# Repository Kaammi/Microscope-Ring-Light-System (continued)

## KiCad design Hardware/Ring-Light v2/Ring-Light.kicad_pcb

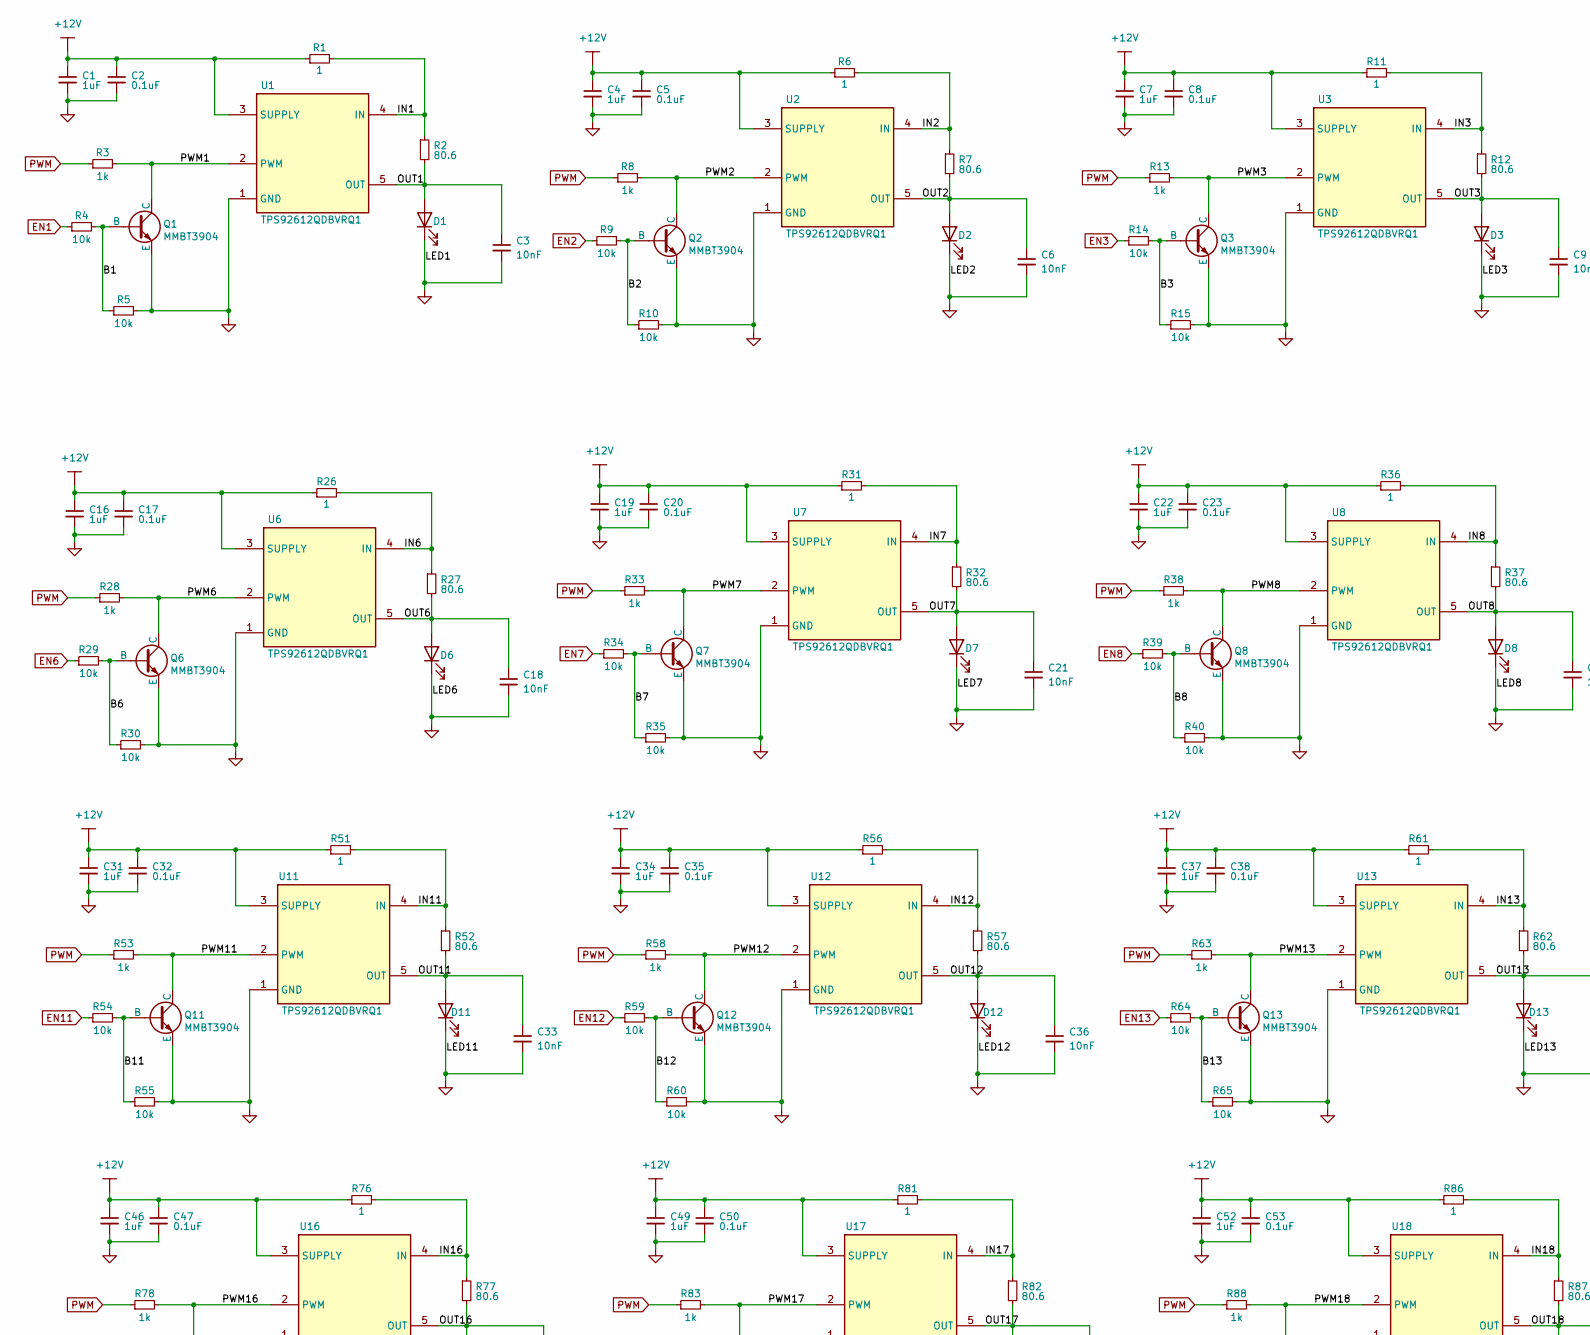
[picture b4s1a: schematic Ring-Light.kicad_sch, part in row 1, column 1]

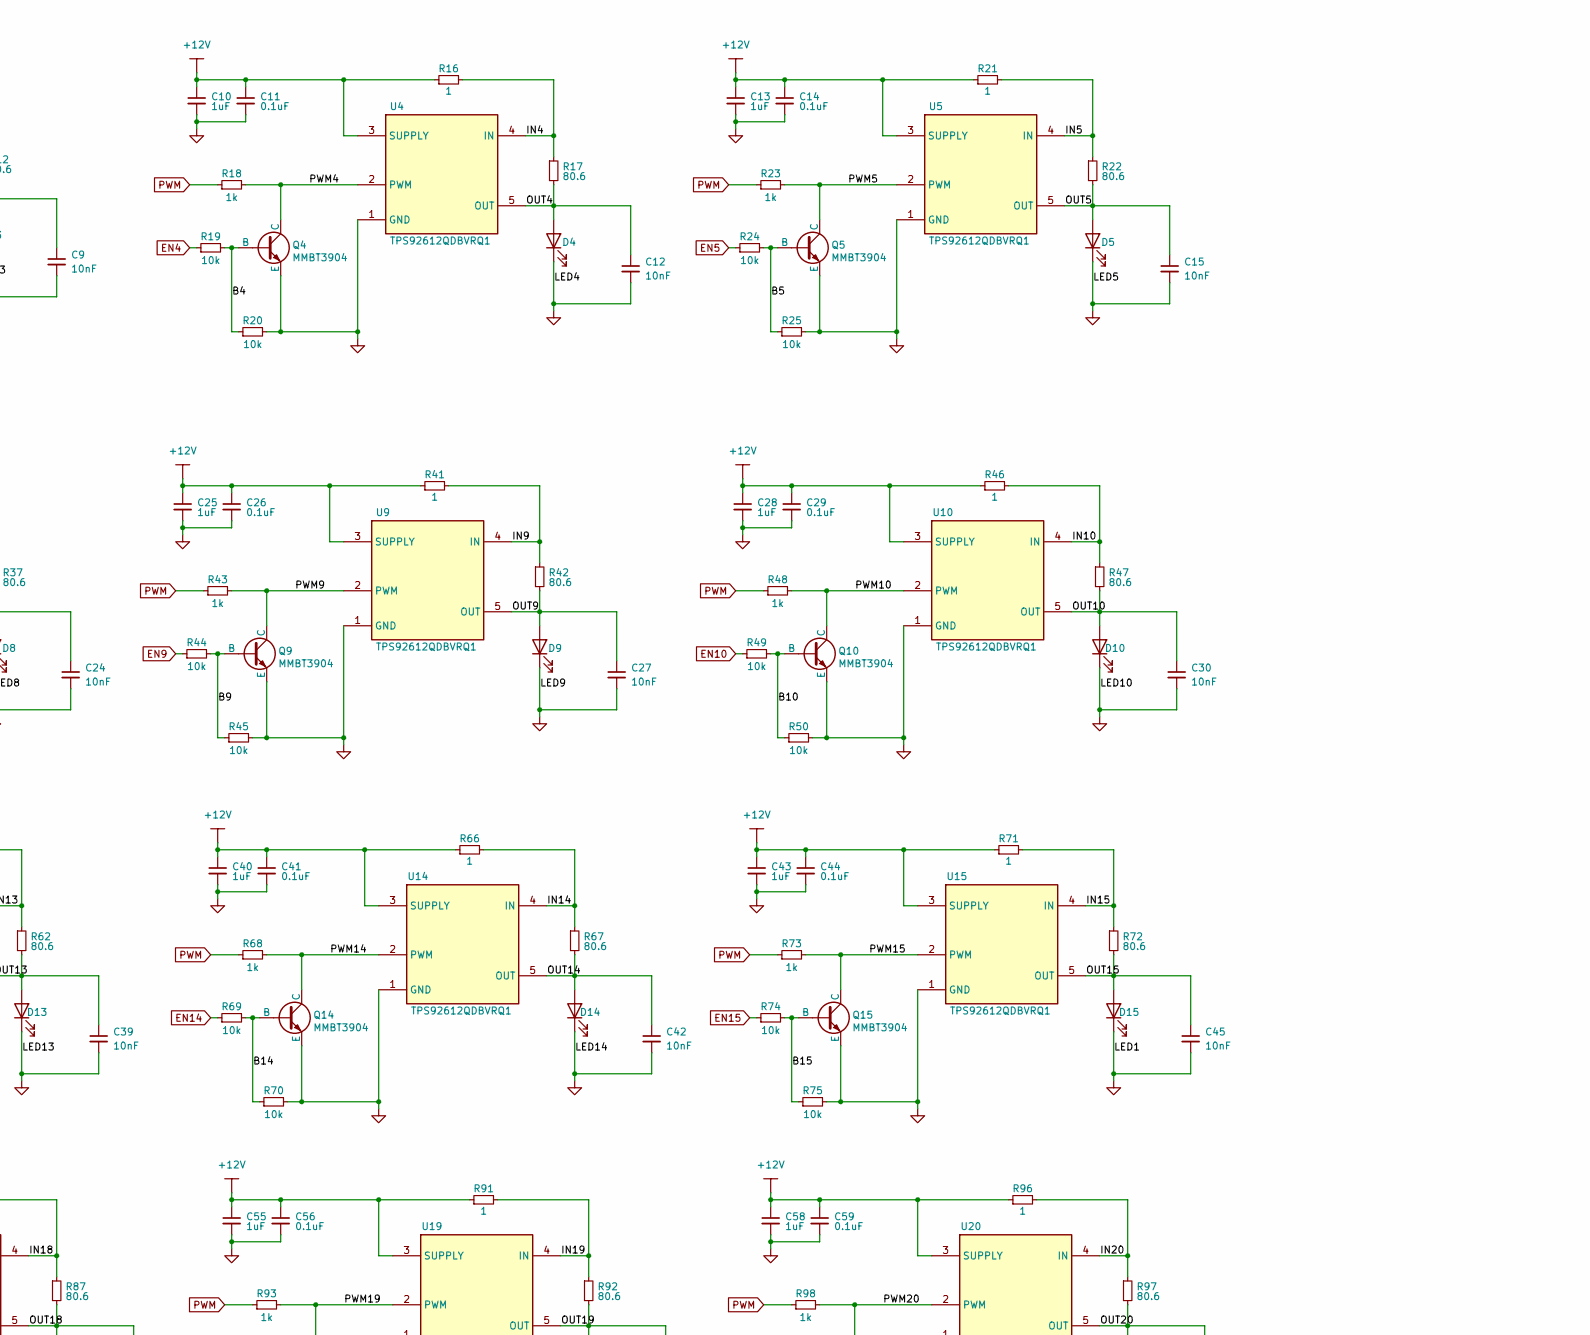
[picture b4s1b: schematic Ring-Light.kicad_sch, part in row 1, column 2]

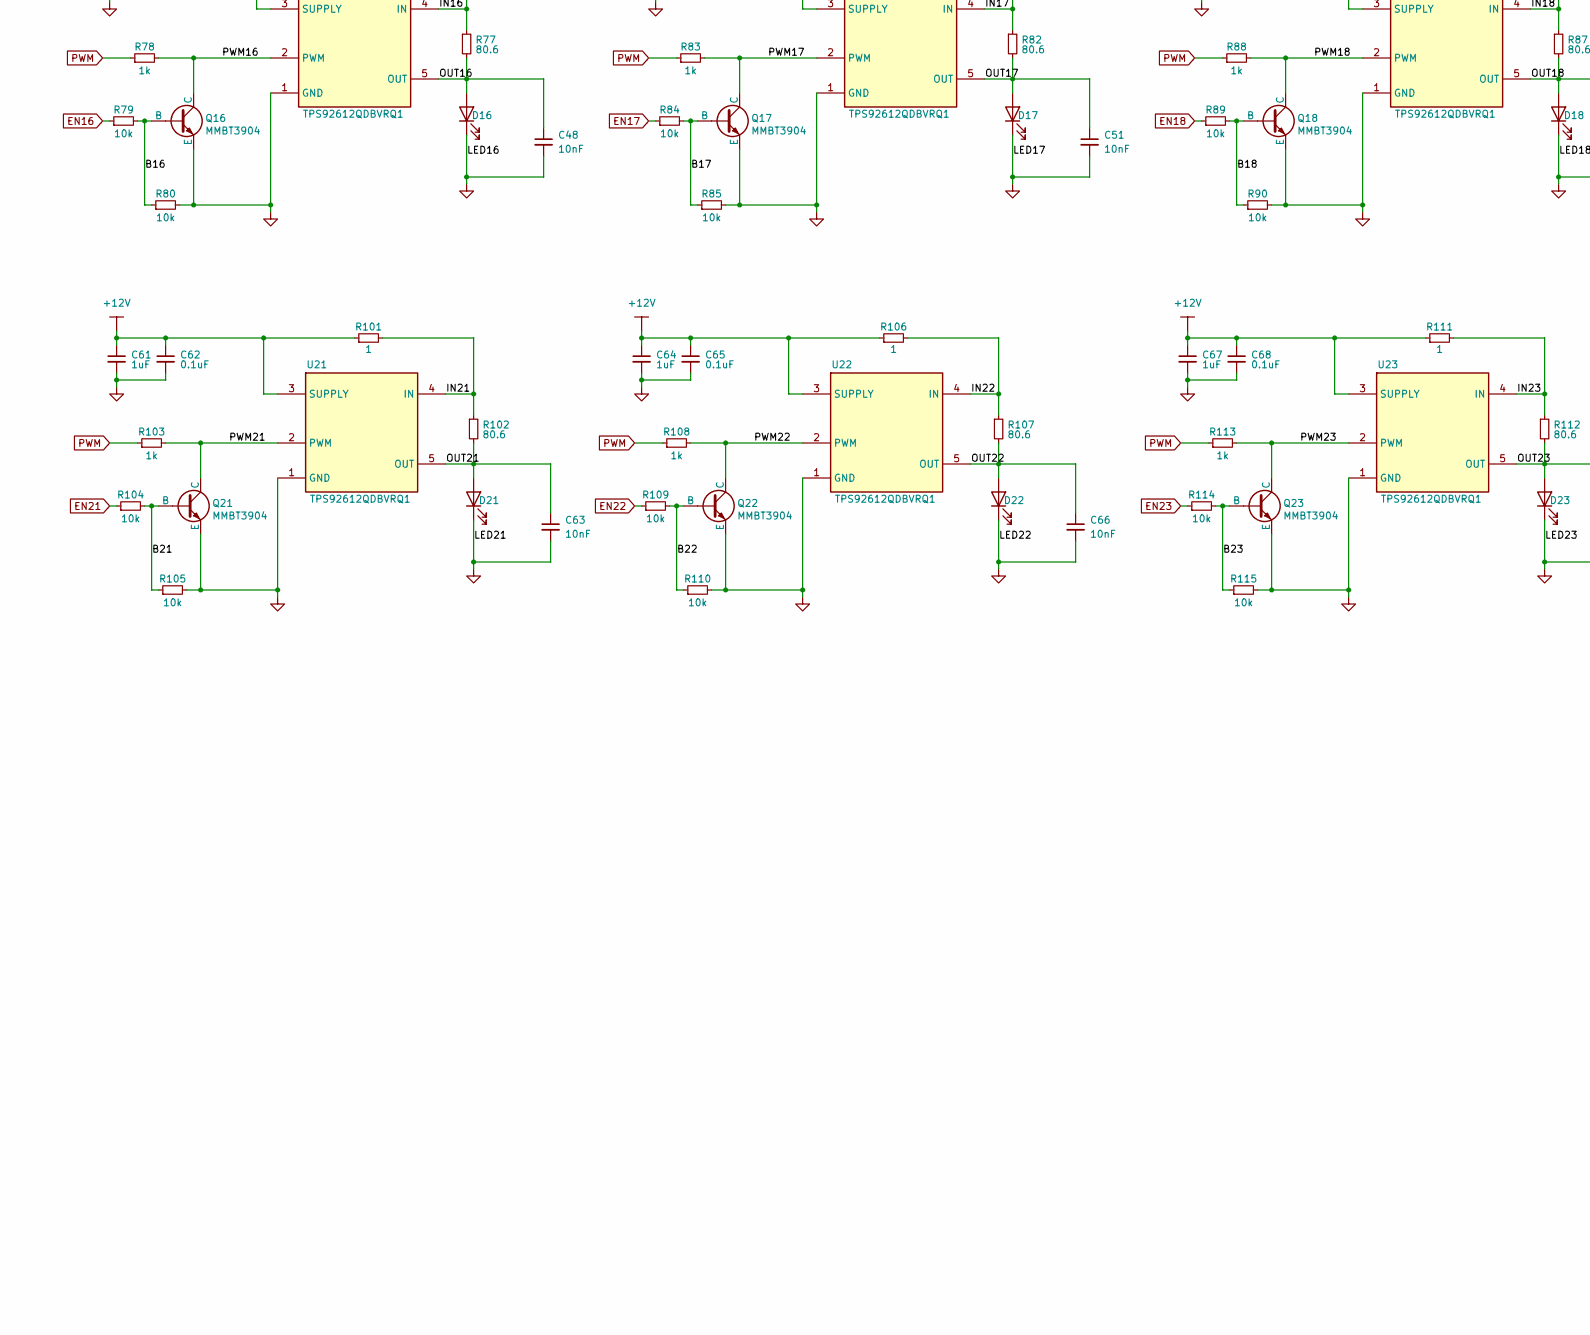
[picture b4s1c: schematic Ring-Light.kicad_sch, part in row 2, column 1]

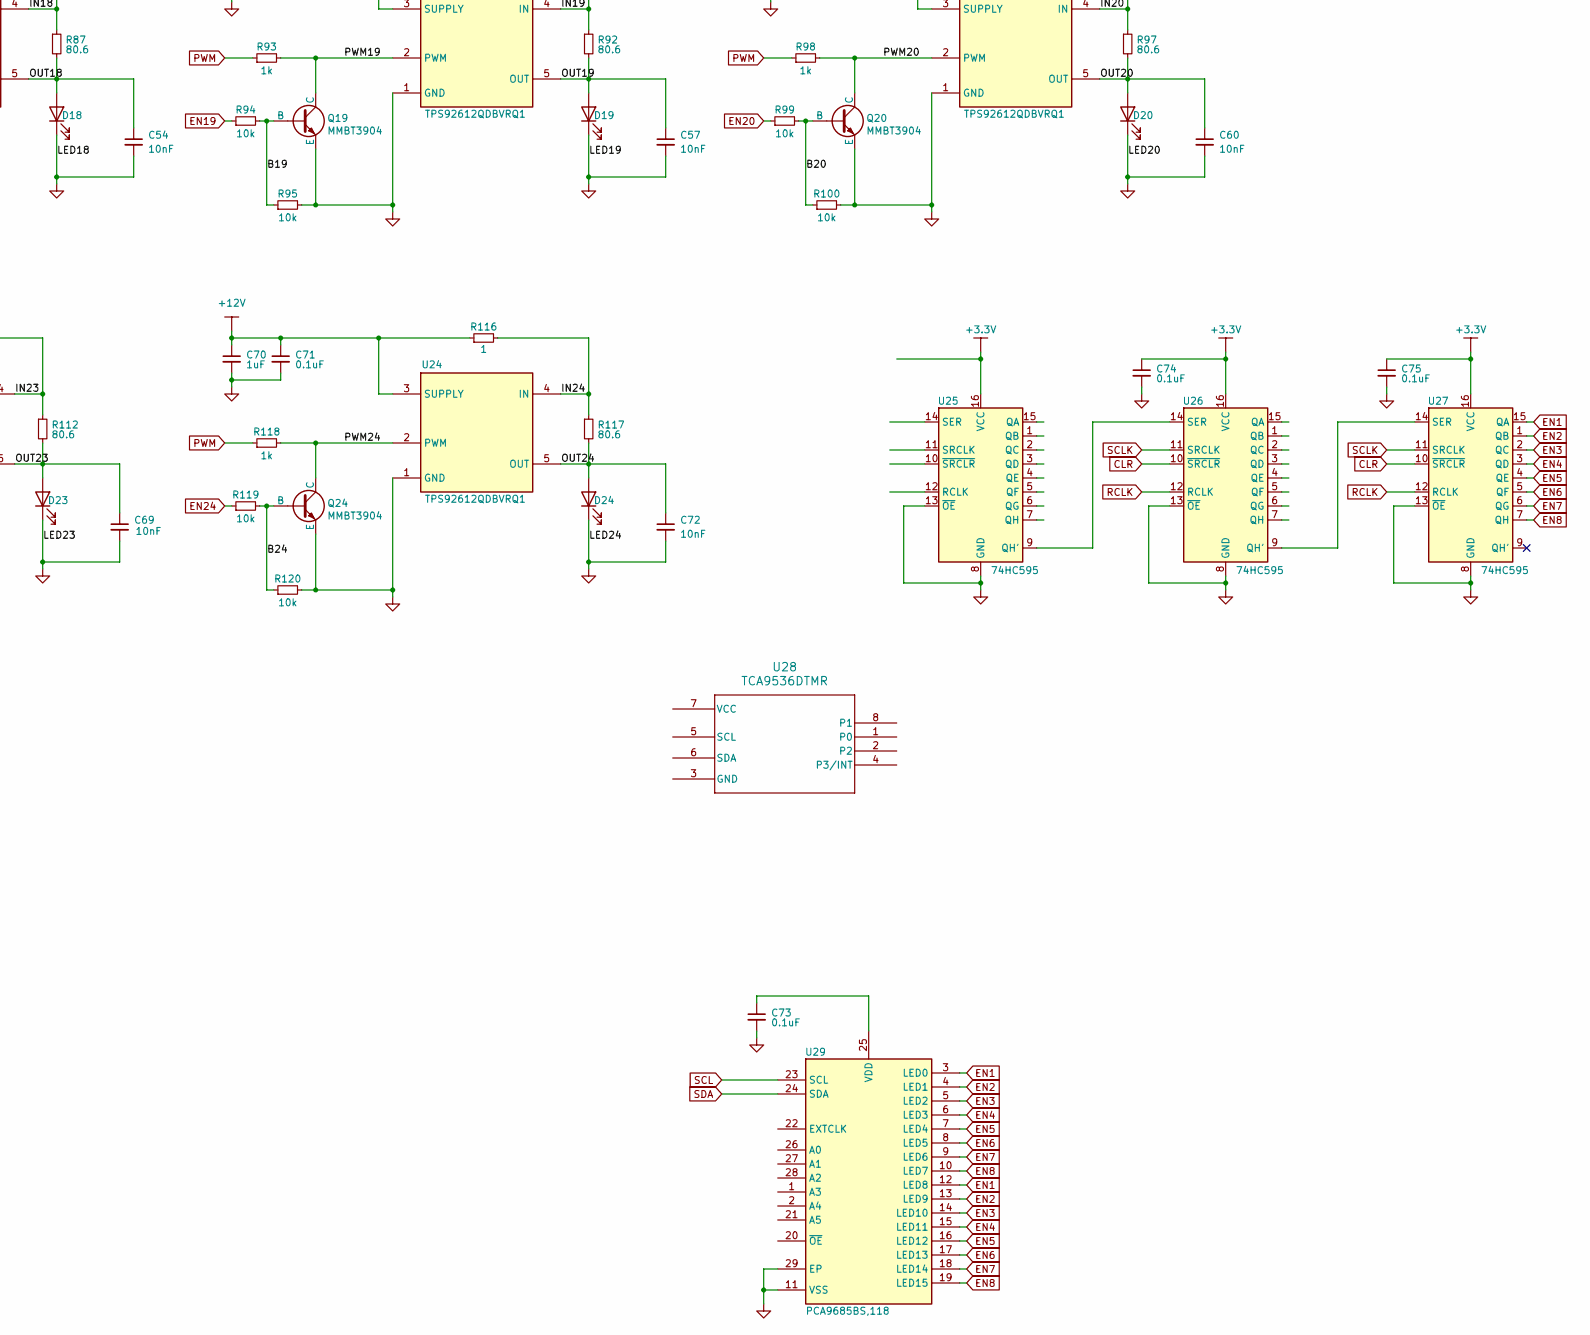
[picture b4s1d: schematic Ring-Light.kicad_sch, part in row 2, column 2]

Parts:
C1, C4, C7, C10, C13, C16, C19, C22, C25, C28, C31, C34, C37, C40, C43, C46, C49, C52, C55, C58, C61, C64, C67, C70: 1uF; C_0805_2012Metric
C2, C5, C8, C11, C14, C17, C20, C23, C26, C29, C32, C35, C38, C41, C44, C47, C50, C53, C56, C59, C62, C65, C68, C71, C73, C74, C75: 0.1uF; C_0603_1608Metric
C3, C6, C9, C12, C15, C18, C21, C24, C27, C30, C33, C36, C39, C42, C45, C48, C51, C54, C57, C60, C63, C66, C69, C72: 10nF; C_0402_1005Metric
D1, D2, D3, D4, D5, D6, D7, D8, D9, D10, D11, D12, D13, D14, D15, D16, D17, D18, D19, D20, D21, D22, D23, D24: LED; GWJTLRS1EMLVL5XX531
Q1, Q2, Q3, Q4, Q5, Q6, Q7, Q8, Q9, Q10, Q11, Q12, Q13, Q14, Q15, Q16, Q17, Q18, Q19, Q20, Q21, Q22, Q23, Q24: MMBT3904; SOT-416
R1, R6, R11, R16, R21, R26, R31, R36, R41, R46, R51, R56, R61, R66, R71, R76, R81, R86, R91, R96, R101, R106, R111, R116: 1; R_0402_1005Metric
R2, R7, R12, R17, R22, R27, R32, R37, R42, R47, R52, R57, R62, R67, R72, R77, R82, R87, R92, R97, R102, R107, R112, R117: 80.6; R_1210_3225Metric
R3, R8, R13, R18, R23, R28, R33, R38, R43, R48, R53, R58, R63, R68, R73, R78, R83, R88, R93, R98, R103, R108, R113, R118: 1k; R_0402_1005Metric
R4, R5, R9, R10, R14, R15, R19, R20, R24, R25, R29, R30, R34, R35, R39, R40, R44, R45, R49, R50, R54, R55, R59, R60, R64, R65, R69, R70, R74, R75, R79, R80, R84, R85, R89, R90, R94, R95, R99, R100, R104, R105, R109, R110, R114, R115, R119, R120: 10k; R_0402_1005Metric
U1, U2, U3, U4, U5, U6, U7, U8, U9, U10, U11, U12, U13, U14, U15, U16, U17, U18, U19, U20, U21, U22, U23, U24: TPS92612QDBVRQ1; SOT95P280X145-5N; Manufacturer_Part_Number TPS92612QDBVRQ1; Mouser Part Number 595-TPS92612QDBVRQ1
U25, U26, U27: 74HC595; 74AHC595BQ115
U28: TCA9536DTMR; X2SON8_DTM_TEX
U29: PCA9685BS,118; QFN65P600X600X100-29N-D; Manufacturer_Part_Number PCA9685BS,118; Mouser Part Number 771-PCA9685BS118

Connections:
+3.3V: C73.1, C74.1, C75.1, U25.16 (VCC), U26.16 (VCC), U27.16 (VCC), U29.25 (VDD)
+12V: C1.1, C2.1, C4.1, C5.1, C7.1, C8.1, C10.1, C11.1, C13.1, C14.1, C16.1, C17.1, C19.1, C20.1, C22.1, C23.1, C25.1, C26.1, C28.1, C29.1, C31.1, C32.1, C34.1, C35.1, C37.1, C38.1, C40.1, C41.1, C43.1, C44.1, C46.1, C47.1, C49.1, C50.1, C52.1, C53.1, C55.1, C56.1, C58.1, C59.1, C61.1, C62.1, C64.1, C65.1, C67.1, C68.1, C70.1, C71.1, R1.1, R6.1, R11.1, R16.1, R21.1, R26.1, R31.1, R36.1, R41.1, R46.1, R51.1, R56.1, R61.1, R66.1, R71.1, R76.1, R81.1, R86.1, R91.1, R96.1, R101.1, R106.1, R111.1, R116.1, U1.3 (SUPPLY), U2.3 (SUPPLY), U3.3 (SUPPLY), U4.3 (SUPPLY), U5.3 (SUPPLY), U6.3 (SUPPLY), U7.3 (SUPPLY), U8.3 (SUPPLY), U9.3 (SUPPLY), U10.3 (SUPPLY), U11.3 (SUPPLY), U12.3 (SUPPLY), U13.3 (SUPPLY), U14.3 (SUPPLY), U15.3 (SUPPLY), U16.3 (SUPPLY), U17.3 (SUPPLY), U18.3 (SUPPLY), U19.3 (SUPPLY), U20.3 (SUPPLY), U21.3 (SUPPLY), U22.3 (SUPPLY), U23.3 (SUPPLY), U24.3 (SUPPLY)
/B1: Q1.1 (B), R4.2, R5.1
/B2: Q2.1 (B), R9.2, R10.1
/B3: Q3.1 (B), R14.2, R15.1
/B4: Q4.1 (B), R19.2, R20.1
/B5: Q5.1 (B), R24.2, R25.1
/B6: Q6.1 (B), R29.2, R30.1
/B7: Q7.1 (B), R34.2, R35.1
/B8: Q8.1 (B), R39.2, R40.1
/B9: Q9.1 (B), R44.2, R45.1
/B10: Q10.1 (B), R49.2, R50.1
/B11: Q11.1 (B), R54.2, R55.1
/B12: Q12.1 (B), R59.2, R60.1
/B13: Q13.1 (B), R64.2, R65.1
/B14: Q14.1 (B), R69.2, R70.1
/B15: Q15.1 (B), R74.2, R75.1
/B16: Q16.1 (B), R79.2, R80.1
/B17: Q17.1 (B), R84.2, R85.1
/B18: Q18.1 (B), R89.2, R90.1
/B19: Q19.1 (B), R94.2, R95.1
/B20: Q20.1 (B), R99.2, R100.1
/B21: Q21.1 (B), R104.2, R105.1
/B22: Q22.1 (B), R109.2, R110.1
/B23: Q23.1 (B), R114.2, R115.1
/B24: Q24.1 (B), R119.2, R120.1
/IN1: R1.2, R2.1, U1.4 (IN)
/IN2: R6.2, R7.1, U2.4 (IN)
/IN3: R11.2, R12.1, U3.4 (IN)
/IN4: R16.2, R17.1, U4.4 (IN)
/IN5: R21.2, R22.1, U5.4 (IN)
/IN6: R26.2, R27.1, U6.4 (IN)
/IN7: R31.2, R32.1, U7.4 (IN)
/IN8: R36.2, R37.1, U8.4 (IN)
/IN9: R41.2, R42.1, U9.4 (IN)
/IN10: R46.2, R47.1, U10.4 (IN)
/IN11: R51.2, R52.1, U11.4 (IN)
/IN12: R56.2, R57.1, U12.4 (IN)
/IN13: R61.2, R62.1, U13.4 (IN)
/IN14: R66.2, R67.1, U14.4 (IN)
/IN15: R71.2, R72.1, U15.4 (IN)
/IN16: R76.2, R77.1, U16.4 (IN)
/IN17: R81.2, R82.1, U17.4 (IN)
/IN18: R86.2, R87.1, U18.4 (IN)
/IN19: R91.2, R92.1, U19.4 (IN)
/IN20: R96.2, R97.1, U20.4 (IN)
/IN21: R101.2, R102.1, U21.4 (IN)
/IN22: R106.2, R107.1, U22.4 (IN)
/IN23: R111.2, R112.1, U23.4 (IN)
/IN24: R116.2, R117.1, U24.4 (IN)
/OUT1: C3.1, D1.3 (A), D1.4 (A), R2.2, U1.5 (OUT)
/OUT2: C6.1, D2.3 (A), D2.4 (A), R7.2, U2.5 (OUT)
/OUT3: C9.1, D3.3 (A), D3.4 (A), R12.2, U3.5 (OUT)
/OUT4: C12.1, D4.3 (A), D4.4 (A), R17.2, U4.5 (OUT)
/OUT5: C15.1, D5.3 (A), D5.4 (A), R22.2, U5.5 (OUT)
/OUT6: C18.1, D6.3 (A), D6.4 (A), R27.2, U6.5 (OUT)
/OUT7: C21.1, D7.3 (A), D7.4 (A), R32.2, U7.5 (OUT)
/OUT8: C24.1, D8.3 (A), D8.4 (A), R37.2, U8.5 (OUT)
/OUT9: C27.1, D9.3 (A), D9.4 (A), R42.2, U9.5 (OUT)
/OUT10: C30.1, D10.3 (A), D10.4 (A), R47.2, U10.5 (OUT)
/OUT11: C33.1, D11.3 (A), D11.4 (A), R52.2, U11.5 (OUT)
/OUT12: C36.1, D12.3 (A), D12.4 (A), R57.2, U12.5 (OUT)
/OUT13: C39.1, D13.3 (A), D13.4 (A), R62.2, U13.5 (OUT)
/OUT14: C42.1, D14.3 (A), D14.4 (A), R67.2, U14.5 (OUT)
/OUT15: C45.1, D15.3 (A), D15.4 (A), R72.2, U15.5 (OUT)
/OUT16: C48.1, D16.3 (A), D16.4 (A), R77.2, U16.5 (OUT)
/OUT17: C51.1, D17.3 (A), D17.4 (A), R82.2, U17.5 (OUT)
/OUT18: C54.1, D18.3 (A), D18.4 (A), R87.2, U18.5 (OUT)
/OUT19: C57.1, D19.3 (A), D19.4 (A), R92.2, U19.5 (OUT)
/OUT20: C60.1, D20.3 (A), D20.4 (A), R97.2, U20.5 (OUT)
/OUT21: C63.1, D21.3 (A), D21.4 (A), R102.2, U21.5 (OUT)
/OUT22: C66.1, D22.3 (A), D22.4 (A), R107.2, U22.5 (OUT)
/OUT23: C69.1, D23.3 (A), D23.4 (A), R112.2, U23.5 (OUT)
/OUT24: C72.1, D24.3 (A), D24.4 (A), R117.2, U24.5 (OUT)
/PWM1: Q1.3 (C), R3.2, U1.2 (PWM)
/PWM2: Q2.3 (C), R8.2, U2.2 (PWM)
/PWM3: Q3.3 (C), R13.2, U3.2 (PWM)
/PWM4: Q4.3 (C), R18.2, U4.2 (PWM)
/PWM5: Q5.3 (C), R23.2, U5.2 (PWM)
/PWM6: Q6.3 (C), R28.2, U6.2 (PWM)
/PWM7: Q7.3 (C), R33.2, U7.2 (PWM)
/PWM8: Q8.3 (C), R38.2, U8.2 (PWM)
/PWM9: Q9.3 (C), R43.2, U9.2 (PWM)
/PWM10: Q10.3 (C), R48.2, U10.2 (PWM)
/PWM11: Q11.3 (C), R53.2, U11.2 (PWM)
/PWM12: Q12.3 (C), R58.2, U12.2 (PWM)
/PWM13: Q13.3 (C), R63.2, U13.2 (PWM)
/PWM14: Q14.3 (C), R68.2, U14.2 (PWM)
/PWM15: Q15.3 (C), R73.2, U15.2 (PWM)
/PWM16: Q16.3 (C), R78.2, U16.2 (PWM)
/PWM17: Q17.3 (C), R83.2, U17.2 (PWM)
/PWM18: Q18.3 (C), R88.2, U18.2 (PWM)
/PWM19: Q19.3 (C), R93.2, U19.2 (PWM)
/PWM20: Q20.3 (C), R98.2, U20.2 (PWM)
/PWM21: Q21.3 (C), R103.2, U21.2 (PWM)
/PWM22: Q22.3 (C), R108.2, U22.2 (PWM)
/PWM23: Q23.3 (C), R113.2, U23.2 (PWM)
/PWM24: Q24.3 (C), R118.2, U24.2 (PWM)
CLR: U25.10 (~SRCLR), U26.10 (~SRCLR), U27.10 (~SRCLR)
EN1: R4.1, U25.15 (QA), U26.15 (QA), U27.15 (QA), U29.3 (LED0), U29.12 (LED8)
EN2: R9.1, U25.1 (QB), U26.1 (QB), U27.1 (QB), U29.4 (LED1), U29.13 (LED9)
EN3: R14.1, U25.2 (QC), U26.2 (QC), U27.2 (QC), U29.5 (LED2), U29.14 (LED10)
EN4: R19.1, U25.3 (QD), U26.3 (QD), U27.3 (QD), U29.6 (LED3), U29.15 (LED11)
EN5: R24.1, U25.4 (QE), U26.4 (QE), U27.4 (QE), U29.7 (LED4), U29.16 (LED12)
EN6: R29.1, U25.5 (QF), U26.5 (QF), U27.5 (QF), U29.8 (LED5), U29.17 (LED13)
EN7: R34.1, U25.6 (QG), U26.6 (QG), U27.6 (QG), U29.9 (LED6), U29.18 (LED14)
EN8: R39.1, U25.7 (QH), U26.7 (QH), U27.7 (QH), U29.10 (LED7), U29.19 (LED15)
EN9: R44.1
EN10: R49.1
EN11: R54.1
EN12: R59.1
EN13: R64.1
EN14: R69.1
EN15: R74.1
EN16: R79.1
EN17: R84.1
EN18: R89.1
EN19: R94.1
EN20: R99.1
EN21: R104.1
EN22: R109.1
EN23: R114.1
EN24: R119.1
GND: C1.2, C2.2, C3.2, C4.2, C5.2, C6.2, C7.2, C8.2, C9.2, C10.2, C11.2, C12.2, C13.2, C14.2, C15.2, C16.2, C17.2, C18.2, C19.2, C20.2, C21.2, C22.2, C23.2, C24.2, C25.2, C26.2, C27.2, C28.2, C29.2, C30.2, C31.2, C32.2, C33.2, C34.2, C35.2, C36.2, C37.2, C38.2, C39.2, C40.2, C41.2, C42.2, C43.2, C44.2, C45.2, C46.2, C47.2, C48.2, C49.2, C50.2, C51.2, C52.2, C53.2, C54.2, C55.2, C56.2, C57.2, C58.2, C59.2, C60.2, C61.2, C62.2, C63.2, C64.2, C65.2, C66.2, C67.2, C68.2, C69.2, C70.2, C71.2, C72.2, C73.2, C74.2, C75.2, D1.1 (K), D1.2 (K), D2.1 (K), D2.2 (K), D3.1 (K), D3.2 (K), D4.1 (K), D4.2 (K), D5.1 (K), D5.2 (K), D6.1 (K), D6.2 (K), D7.1 (K), D7.2 (K), D8.1 (K), D8.2 (K), D9.1 (K), D9.2 (K), D10.1 (K), D10.2 (K), D11.1 (K), D11.2 (K), D12.1 (K), D12.2 (K), D13.1 (K), D13.2 (K), D14.1 (K), D14.2 (K), D15.1 (K), D15.2 (K), D16.1 (K), D16.2 (K), D17.1 (K), D17.2 (K), D18.1 (K), D18.2 (K), D19.1 (K), D19.2 (K), D20.1 (K), D20.2 (K), D21.1 (K), D21.2 (K), D22.1 (K), D22.2 (K), D23.1 (K), D23.2 (K), D24.1 (K), D24.2 (K), Q1.2 (E), Q2.2 (E), Q3.2 (E), Q4.2 (E), Q5.2 (E), Q6.2 (E), Q7.2 (E), Q8.2 (E), Q9.2 (E), Q10.2 (E), Q11.2 (E), Q12.2 (E), Q13.2 (E), Q14.2 (E), Q15.2 (E), Q16.2 (E), Q17.2 (E), Q18.2 (E), Q19.2 (E), Q20.2 (E), Q21.2 (E), Q22.2 (E), Q23.2 (E), Q24.2 (E), R5.2, R10.2, R15.2, R20.2, R25.2, R30.2, R35.2, R40.2, R45.2, R50.2, R55.2, R60.2, R65.2, R70.2, R75.2, R80.2, R85.2, R90.2, R95.2, R100.2, R105.2, R110.2, R115.2, R120.2, U1.1 (GND), U2.1 (GND), U3.1 (GND), U4.1 (GND), U5.1 (GND), U6.1 (GND), U7.1 (GND), U8.1 (GND), U9.1 (GND), U10.1 (GND), U11.1 (GND), U12.1 (GND), U13.1 (GND), U14.1 (GND), U15.1 (GND), U16.1 (GND), U17.1 (GND), U18.1 (GND), U19.1 (GND), U20.1 (GND), U21.1 (GND), U22.1 (GND), U23.1 (GND), U24.1 (GND), U25.8 (GND), U25.13 (~OE), U26.8 (GND), U26.13 (~OE), U27.8 (GND), U27.13 (~OE), U29.11 (VSS), U29.29 (EP)
unnamed: U25.9 (QH'), U26.14 (SER)
unnamed: U26.9 (QH'), U27.14 (SER)
PWM: R3.1, R8.1, R13.1, R18.1, R23.1, R28.1, R33.1, R38.1, R43.1, R48.1, R53.1, R58.1, R63.1, R68.1, R73.1, R78.1, R83.1, R88.1, R93.1, R98.1, R103.1, R108.1, R113.1, R118.1
RCLK: U25.12 (RCLK), U26.12 (RCLK), U27.12 (RCLK)
SCLK: U25.11 (SRCLK), U26.11 (SRCLK), U27.11 (SRCLK)
SDA: U25.14 (SER)

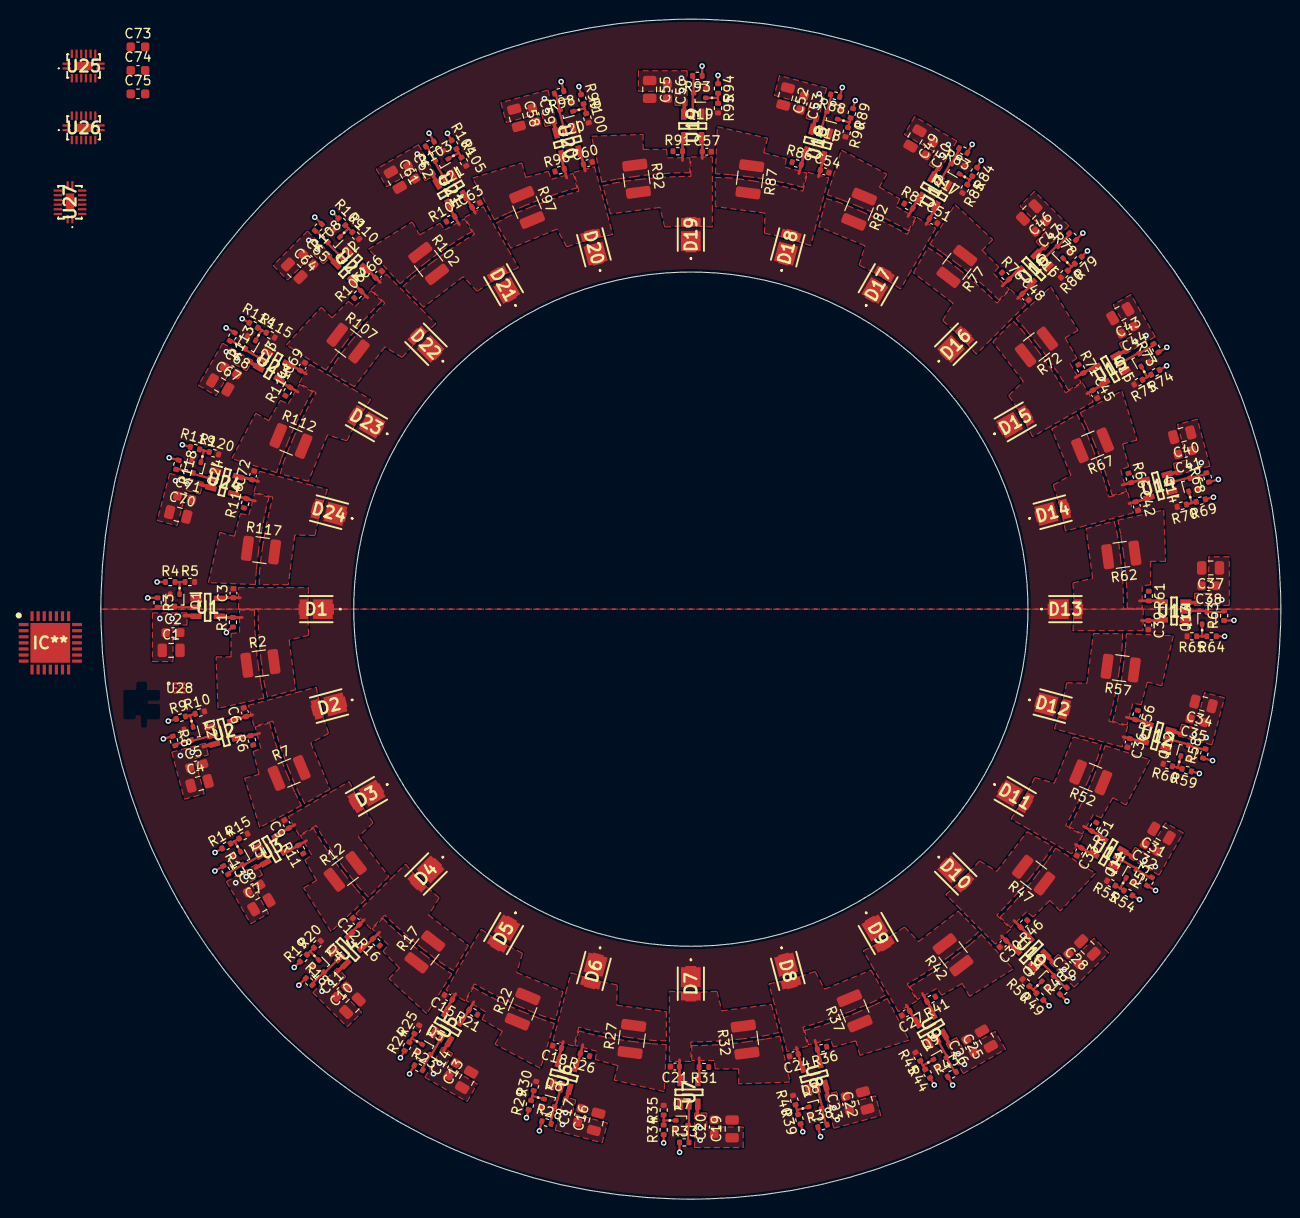
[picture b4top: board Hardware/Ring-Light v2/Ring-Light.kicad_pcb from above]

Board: 4 copper layers, 126.0 x 126.0 mm, 272 parts (0 on the bottom side), 113 nets.

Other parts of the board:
IC**: QFN65P600X600X100-29N-D

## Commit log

2026-02-09 init
